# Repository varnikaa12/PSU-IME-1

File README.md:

# PSU-IME-1

The Harold & Inge Marcus Department of Industrial & Manufacturing Engineering at The Pennsylvania
State University is launching a new course in industrial automation and robotics. They are seeking a low-
cost, open-source, and modular tabletop training platform that supports hands-on learning in industrial
control systems, programmable logic controllers (PLCs), system integration, and digital twins while
currently lacking an affordable, modular physical platform for lab instruction. The department's existing
commercial training devices provide strong functionality but are too expensive, closed, and difficult to
modify or repair, limiting their suitability for long-term academic use and iterative student prototyping.
The student team will design and prototype an MVP tabletop production cell that sorts small colored
cylinders representing workpieces in a manufacturing line. Key requirements include modular and
reconfigurable mechanical design, predominantly 3D-printed or easily fabricated components, low
assembly complexity, 24V PLC compatibility using ladder logic via OpenPLC on RevPi hardware,
minimized custom electronics, and sourcing of all major components from established suppliers. In-scope
activities include mechanical design using primarily 3D-printed components, integration of 24 V
electrical hardware aligned with IEC 61131-2/3, PLC-based control logic, industrial sensor integration,
and development of a digital twin in ProtoTwin. Stretch goals include multi-size LEGO sorting, a bulk
hopper with automatic singulation, and interoperability with other tabletop cells to create an end-to-end
automated workflow.
Core deliverables include: (1) a working physical prototype suitable for classroom demonstrations, (2)
complete open-source documentation including CAD, bill of materials, assembly drawings, wiring
diagrams, and source code, and (3) a validated ProtoTwin model of the system. Key budget requirements
include a target build cost of approximately $100 per unit with an absolute maximum of $500. Expected
benefits include substantial cost reduction relative to commercial trainers, improved instructional quality
through hands-on interaction with industrial hardware, reduced setup and maintenance effort, and a
flexible open-source platform that future cohorts can modify, repair, and extend. The project is planned
for 15 weeks, starting January 12th and ending by May 3rd with the Capstone Showcase and Program
Closeout Review.

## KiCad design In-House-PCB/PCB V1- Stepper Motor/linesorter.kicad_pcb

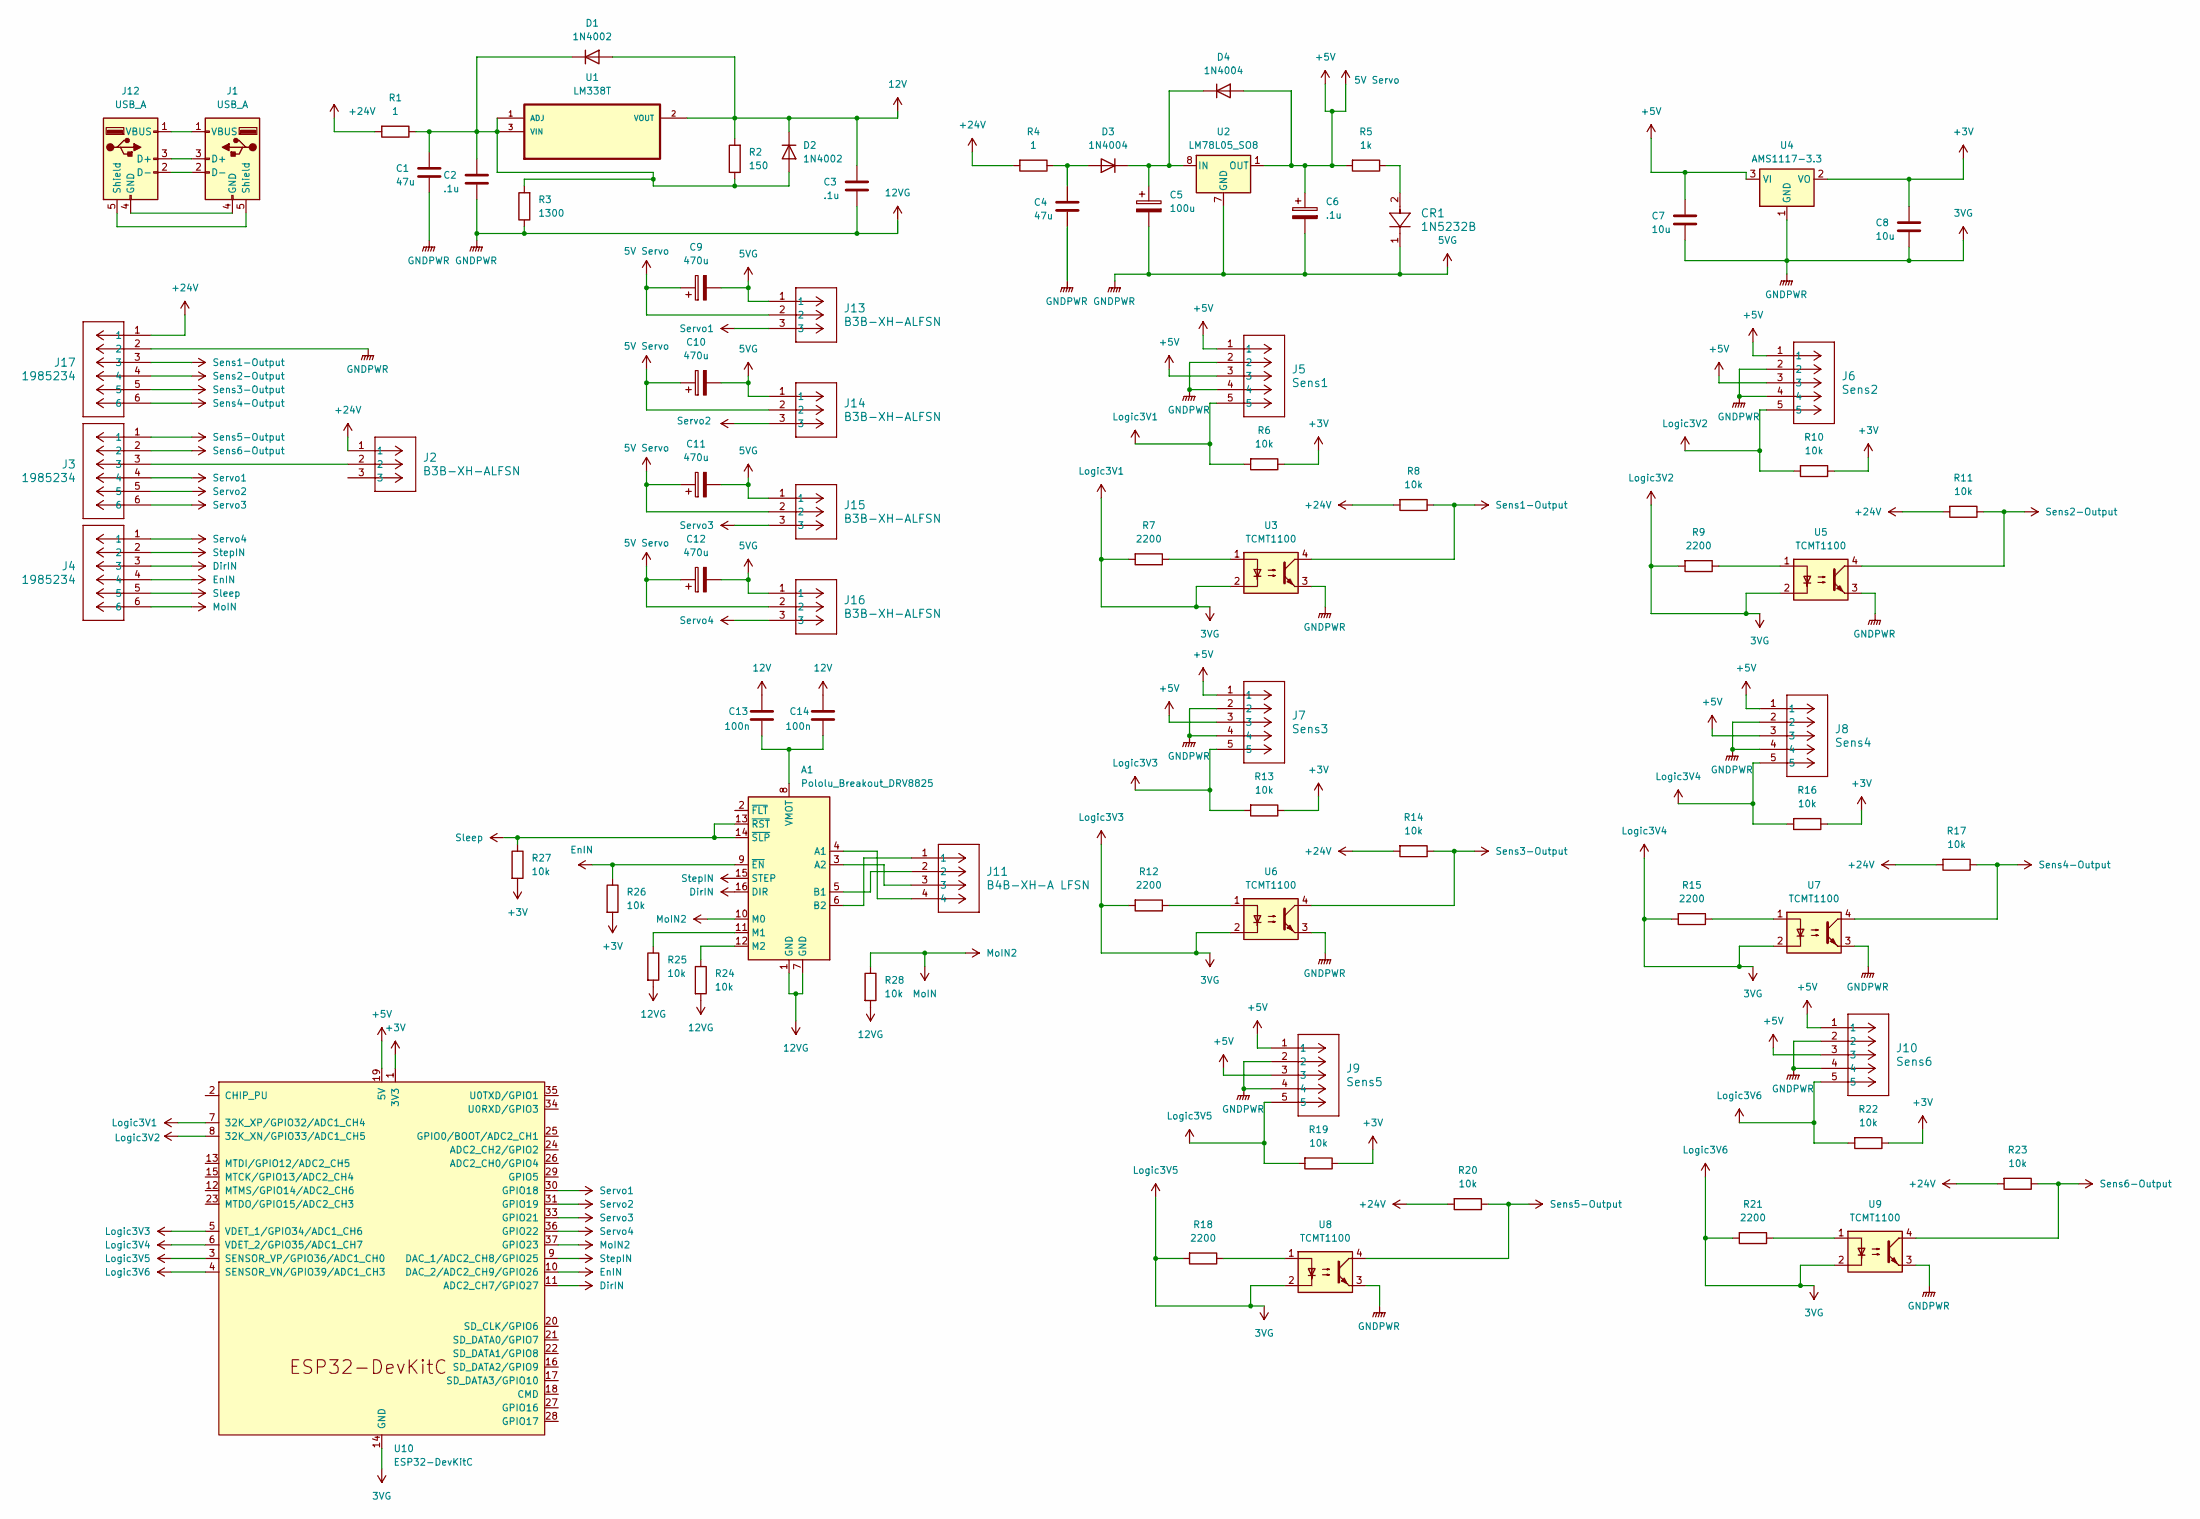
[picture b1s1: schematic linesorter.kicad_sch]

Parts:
A1: Pololu_Breakout_DRV8825; Pololu_Breakout-16_15.2x20.3mm
C1, C4: 47u; C_0201_0603Metric
C2, C3: .1u; C_0201_0603Metric
C5: 100u; CP_Elec_3x5.3
C6: .1u; CP_Elec_3x5.3
C7, C8: 10u; C_0201_0603Metric
C9, C10, C11, C12: 470u; CP_Elec_3x5.3
C13, C14: 100n; C_0201_0603Metric
CR1: 1N5232B; AFL-W2C8.9D
D1, D2: 1N4002; D_DO-41_SOD81_P10.16mm_Horizontal
D3, D4: 1N4004; D_DO-41_SOD81_P10.16mm_Horizontal
J1, J12: USB_A; USB_A_Connfly_DS1095
J2, J13, J14, J15, J16: B3B-XH-ALFSN; CONN_B3B-XH-A_JST
J3, J4, J17: 1985234; CONN_1985234
J5: Sens1; CONN_S5B-PH-K-S_JST
J6: Sens2; CONN_S5B-PH-K-S_JST
J7: Sens3; CONN_S5B-PH-K-S_JST
J8: Sens4; CONN_S5B-PH-K-S_JST
J9: Sens5; CONN_S5B-PH-K-S_JST
J10: Sens6; CONN_S5B-PH-K-S_JST
J11: B4B-XH-A LFSN; CONN_B4B-XH-A LFSN_JST
R1, R4: 1; R_0201_0603Metric
R2: 150; R_0201_0603Metric
R3: 1300; R_0201_0603Metric
R5: 1k; R_0201_0603Metric
R6, R8, R10, R11, R13, R14, R16, R17, R19, R20, R22, R23, R24, R25, R26, R27, R28: 10k; R_0201_0603Metric
R7, R9, R12, R15, R18, R21: 2200; R_0201_0603Metric
U1: LM338T; TO254P1054X470X1955-3
U2: LM78L05_SO8; SOIC-8_3.9x4.9mm_P1.27mm
U3, U5, U6, U7, U8, U9: TCMT1100; SOP-4_4.4x2.6mm_P1.27mm
U4: AMS1117-3.3; SOT-223-3_TabPin2
U10: ESP32-DevKitC

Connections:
12V: C3.1, C13.1, C14.1, D1.2 (A), D2.1 (K), R2.2, U1.2 (VOUT)
12VG: A1.1 (GND), A1.7 (GND), C1.2, C2.2, C3.2, C4.2, C5.2, C6.2, C7.2, C8.2, C9.2, C10.2, C11.2, C12.2, CR1.1, J5.2, J5.4, J5.5, J6.2, J6.4, J6.5, J7.2, J7.4, J7.5, J8.2, J8.4, J8.5, J9.2, J9.4, J9.5, J10.2, J10.4, J10.5, J13.1, J14.1, J15.1, J16.1, J17.2, R3.1, R6.2, R7.2, R9.2, R10.2, R12.2, R13.2, R15.2, R16.2, R18.2, R19.2, R21.2, R22.2, R24.2, R25.2, R28.2, U2.2 (GND), U2.3 (GND), U2.6 (GND), U2.7 (GND), U3.2, U3.3, U4.1 (GND), U5.2, U5.3, U6.2, U6.3, U7.2, U7.3, U8.2, U8.3, U9.2, U9.3, U10.3 (SENSOR_VP/GPIO36/ADC1_CH0), U10.4 (SENSOR_VN/GPIO39/ADC1_CH3), U10.5 (VDET_1/GPIO34/ADC1_CH6), U10.6 (VDET_2/GPIO35/ADC1_CH7), U10.7 (32K_XP/GPIO32/ADC1_CH4), U10.8 (32K_XN/GPIO33/ADC1_CH5), U10.14 (GND), U10.32 (GND), U10.38 (GND)
+3V: C8.1, R6.1, R10.1, R13.1, R16.1, R19.1, R22.1, R26.2, R27.2, U4.2 (VO), U10.1 (3V3)
+5V: C6.1, C7.1, C9.1, C10.1, C11.1, C12.1, D4.2 (A), J5.1, J5.3, J6.1, J6.3, J7.1, J7.3, J8.1, J8.3, J9.1, J9.3, J10.1, J10.3, J13.2, J14.2, J15.2, J16.2, R5.2, U2.1 (OUT), U4.3 (VI), U10.19 (5V)
+24V: J2.1, J17.1, R1.2, R4.2, R8.2, R11.2, R14.2, R17.2, R20.2, R23.2
DirIN: A1.16 (DIR), J4.3, U10.11 (ADC2_CH7/GPIO27)
EnIN: A1.9 (~EN), J4.4, R26.1, U10.10 (DAC_2/ADC2_CH9/GPIO26)
MoIN: A1.10 (M0), J4.6, R28.1, U10.37 (GPIO23)
unnamed: A1.4 (A1), J11.4
unnamed: A1.3 (A2), J11.3
unnamed: A1.5 (B1), J11.2
unnamed: A1.6 (B2), J11.1
unnamed: A1.11 (M1), R25.1
unnamed: A1.12 (M2), R24.1
unnamed: A1.8 (VMOT), C13.2, C14.2
unnamed: CR1.2, R5.1
unnamed: C1.1, C2.1, D1.1 (K), D2.2 (A), R1.1, R2.1, R3.2, U1.1 (ADJ), U1.3 (VIN)
unnamed: C4.1, D3.2 (A), R4.1
unnamed: C5.1, D3.1 (K), D4.1 (K), U2.8 (IN)
unnamed: J1.3 (D+), J12.3 (D+)
unnamed: J1.2 (D-), J12.2 (D-)
unnamed: J1.4 (GND), J12.4 (GND)
unnamed: J1.5 (Shield), J12.5 (Shield)
unnamed: J1.1 (VBUS), J12.1 (VBUS)
unnamed: J2.2, J3.3
unnamed: R7.1, U3.1
unnamed: R9.1, U5.1
unnamed: R12.1, U6.1
unnamed: R15.1, U7.1
unnamed: R18.1, U8.1
unnamed: R21.1, U9.1
Sens1-Output: J17.3, R8.1, U3.4
Sens2-Output: J17.4, R11.1, U5.4
Sens3-Output: J17.5, R14.1, U6.4
Sens4-Output: J17.6, R17.1, U7.4
Sens5-Output: J3.1, R20.1, U8.4
Sens6-Output: J3.2, R23.1, U9.4
Servo1: J3.4, J13.3, U10.30 (GPIO18)
Servo2: J3.5, J14.3, U10.31 (GPIO19)
Servo3: J3.6, J15.3, U10.33 (GPIO21)
Servo4: J4.1, J16.3, U10.36 (GPIO22)
Sleep: A1.13 (~RST), A1.14 (~SLP), J4.5, R27.1
StepIN: A1.15 (STEP), J4.2, U10.9 (DAC_1/ADC2_CH8/GPIO25)

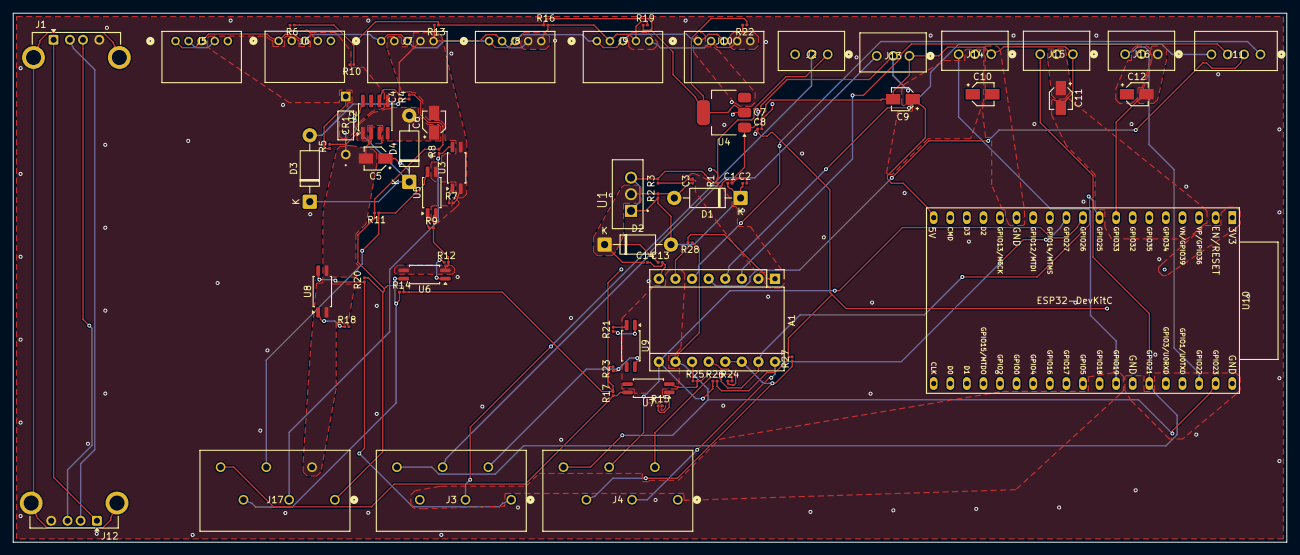
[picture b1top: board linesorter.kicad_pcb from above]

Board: 2 copper layers, 195.0 x 81.0 mm, 75 parts (0 on the bottom side), 43 nets.

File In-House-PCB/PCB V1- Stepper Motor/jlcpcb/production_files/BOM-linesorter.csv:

Comment,Designator,Footprint,LCSC,Quantity
1N4002,"D1,D2",D_DO-41_SOD81_P10.16mm_Horizontal,C18199086,2
1N4004,"D3,D4",D_DO-41_SOD81_P10.16mm_Horizontal,C18199087,2
USB_A,"J1,J12",USB_A_Connfly_DS1095,C6568,2
10k,R8,R_0201_0603Metric,C106225,1
10k,R16,R_0201_0603Metric,C106225,1
470u,C10,CP_Elec_3x5.3,C4747954,1
Sens3,J7,CONN_S5B-PH-K-S_JST,C20089285,1
47u,C1,C_0201_0603Metric,C16780,1
B3B-XH-ALFSN,J15,CONN_B3B-XH-A_JST,C144394,1
470u,C12,CP_Elec_3x5.3,C4747954,1
100n,C13,C_0201_0603Metric,C76934,1
10k,R19,R_0201_0603Metric,C106225,1
1,R1,R_0201_0603Metric,C2484784,1
2200,R21,R_0201_0603Metric,C142018,1
150,R2,R_0201_0603Metric,C295773,1
B3B-XH-ALFSN,J13,CONN_B3B-XH-A_JST,C144394,1
1300,R3,R_0201_0603Metric,C158815,1
Sens6,J10,CONN_S5B-PH-K-S_JST,C20089285,1
10k,R24,R_0201_0603Metric,C106225,1
TCMT1100,U9,SOP-4_4.4x2.6mm_P1.27mm,C118298,1
TCMT1100,U5,SOP-4_4.4x2.6mm_P1.27mm,C118298,1
.1u,C6,CP_Elec_3x5.3,C2887276,1
10u,C7,C_0201_0603Metric,C19702,1
Sens4,J8,CONN_S5B-PH-K-S_JST,C20089285,1
Sens5,J9,CONN_S5B-PH-K-S_JST,C20089285,1
1k,R5,R_0201_0603Metric,C138165,1
B3B-XH-ALFSN,J14,CONN_B3B-XH-A_JST,C144394,1
TCMT1100,U6,SOP-4_4.4x2.6mm_P1.27mm,C118298,1
AMS1117-3.3,U4,SOT-223-3_TabPin2,C6186,1
2200,R18,R_0201_0603Metric,C142018,1
2200,R7,R_0201_0603Metric,C142018,1
1985234,J17,CONN_1985234,C7472154,1
470u,C9,CP_Elec_3x5.3,C4747954,1
B3B-XH-ALFSN,J16,CONN_B3B-XH-A_JST,C144394,1
10k,R14,R_0201_0603Metric,C106225,1
2200,R12,R_0201_0603Metric,C142018,1
10k,R13,R_0201_0603Metric,C106225,1
ESP32-DevKitC,U10,ESP32-DevKitC,C20547324,1
10k,R26,R_0201_0603Metric,C106225,1
TCMT1100,U7,SOP-4_4.4x2.6mm_P1.27mm,C118298,1
1N5232B,CR1,AFL-W2C8.9D,C895243,1
.1u,C3,C_0201_0603Metric,C76930,1
10k,R10,R_0201_0603Metric,C106225,1
470u,C11,CP_Elec_3x5.3,C4747954,1
10k,R11,R_0201_0603Metric,C106225,1
LM78L05_SO8,U2,SOIC-8_3.9x4.9mm_P1.27mm,C596351,1
10k,R28,R_0201_0603Metric,C106225,1
1,R4,R_0201_0603Metric,C2484784,1
47u,C4,C_0201_0603Metric,C16780,1
TCMT1100,U8,SOP-4_4.4x2.6mm_P1.27mm,C118298,1
10k,R22,R_0201_0603Metric,C106225,1
10u,C8,C_0201_0603Metric,C19702,1
10k,R23,R_0201_0603Metric,C106225,1
10k,R25,R_0201_0603Metric,C106225,1
10k,R17,R_0201_0603Metric,C106225,1
Sens2,J6,CONN_S5B-PH-K-S_JST,C20089285,1
TCMT1100,U3,SOP-4_4.4x2.6mm_P1.27mm,C118298,1
B3B-XH-ALFSN,J2,CONN_B3B-XH-A_JST,C144394,1
1985234,J3,CONN_1985234,C7472154,1
2200,R15,R_0201_0603Metric,C142018,1
100u,C5,CP_Elec_3x5.3,C2836443,1
2200,R9,R_0201_0603Metric,C142018,1
10k,R6,R_0201_0603Metric,C106225,1
1985234,J4,CONN_1985234,C7472154,1
10k,R20,R_0201_0603Metric,C106225,1
Sens1,J5,CONN_S5B-PH-K-S_JST,C20089285,1
.1u,C2,C_0201_0603Metric,C76930,1
10k,R27,R_0201_0603Metric,C106225,1
100n,C14,C_0201_0603Metric,C76934,1
LM338T,U1,TO254P1054X470X1955-3,C53303,1
B4B-XH-A LFSN,J11,CONN_B4B-XH-A LFSN_JST,C594232,1

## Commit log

2026-02-10 Enhance README with detailed project overview
    Expanded project description to include course objectives, key requirements, deliverables, budget, and expected benefits.
2026-02-18 Mechanical: File relocation
2026-02-18 Alpha prototype PCB implementatioon
2026-02-18 Electrical: File update
2026-03-05 Beta Prototype update
2026-03-05 init: camera color sensor implementation
2026-03-05 V1.0: Basic color sensor with live feed
2026-03-05 V1.01: Cameras recognized by name not number
2026-03-05 V1.02: Proper exit functionality added
2026-03-05 V1.03: Improved Colour accuracy
2026-03-05 V1.04: Added RevPi Codesys Implementation with local PC being used as MODBUS
2026-03-05 V1.05: README update and patching
2026-03-05 V1.06: More accurate algorithm
2026-03-25 Electrical: PCB V1 Uploaded & Components added
2026-04-02 Color Sensor Code Update
2026-04-02 V2.01: Color Sensor RevPi Algorithm swapped
2026-04-02 V2.02: Whoop dee doo
2026-04-02 V2.03: Wait
2026-04-02 V2.04: Bit masking
2026-04-02 V2.05: Channel 1 oopsie daisy
2026-04-02 working
2026-04-08 Electrical: PCB V2 & Components Added
2026-04-10 esp servo and stepper initial code
2026-04-10 esp servo and stepper start
2026-04-13 added a todo I forgot :(
2026-04-13 belt stopping functionality under camera
    //need to adjust clicks for each of the gates and after how many clicks the belt will stop (when it's under the camera from first breakbeam)
    //need to check about the 21 pinout for blue gate instead of 22 (wasn't working...)
2026-04-15 Current RevPi version
2026-04-15 Uploaded CODESYS Project Archive
2026-04-21 simplified build
2026-04-21 simplified build 2
2026-04-26 Add files via upload
    Mechanical Full Assembly
2026-04-26 Create temp to delete
2026-04-26 Create instructions folder
2026-04-26 final build
2026-04-26 Current CODESYS Project Archive
2026-04-26 Uploaded Final ProtoTwin Project
2026-04-26 Uploaded Final ProtoTwin Video
2026-05-05 Updated Files to be compatible with JLCPCB
2026-05-06 jlc pcb bom update
